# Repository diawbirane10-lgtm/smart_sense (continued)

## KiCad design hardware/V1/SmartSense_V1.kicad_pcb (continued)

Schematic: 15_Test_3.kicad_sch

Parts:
P1, P2, P3: PWR_FLAG; MPN PWR_FLAG

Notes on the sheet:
15 Test 3
Signaux homonymes relies par etiquettes globales ; alimentation 24 V SELV ; prototype a qualifier.
V1 RevA / Validation ERC, DRC et essais du prototype documentes dans le dossier technique.

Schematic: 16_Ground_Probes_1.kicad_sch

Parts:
TP13, TP14, TP15, TP16, TP17, TP18, TP19, TP20: GND; TestPoint_THTPad_D1.0mm_Drill0.5mm; MPN GND probe PCB feature

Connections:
GND: TP13.1, TP14.1, TP15.1, TP16.1, TP17.1, TP18.1, TP19.1, TP20.1; also elsewhere on the board

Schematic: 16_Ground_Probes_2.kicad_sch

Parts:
TP21, TP22, TP23, TP24, TP25, TP26, TP27, TP28: GND; TestPoint_THTPad_D1.0mm_Drill0.5mm; MPN GND probe PCB feature

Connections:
GND: TP21.1, TP22.1, TP23.1, TP24.1, TP25.1, TP26.1, TP27.1, TP28.1; also elsewhere on the board

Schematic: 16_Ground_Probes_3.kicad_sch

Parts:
TP29: GND; TestPoint_THTPad_D1.0mm_Drill0.5mm; MPN GND probe PCB feature

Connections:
GND: TP29.1; also elsewhere on the board

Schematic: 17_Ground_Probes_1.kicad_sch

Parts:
TP30, TP31: GND; TestPoint_THTPad_D1.0mm_Drill0.5mm; MPN GND probe PCB feature

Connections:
GND: TP30.1, TP31.1; also elsewhere on the board

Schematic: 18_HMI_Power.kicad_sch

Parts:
C42: 100u 10V low ESR; CP_Elec_6.3x7.7; MPN EEEFK1A101P
C43: 2.2u 16V X7R; C_0805_2012Metric; MPN C0805C225K4RACTU
C44: 4.7u 10V X7R; C_0805_2012Metric; MPN C0805C475K8RACTU
C47: 100n 100V X7R; C_0805_2012Metric; MPN C0805C104K1RACTU
FB1: 220R@100MHz 2A; R_0805_2012Metric; MPN BLM21PG221SN1D
U13: TLV75533PDBVR; SOT-23-5; MPN TLV75533PDBVR

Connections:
+3V3_HMI: C44.1, U13.5 (OUT); also elsewhere on the board
+5V: FB1.1; also elsewhere on the board
+5V_HMI: C42.1, C43.1, C47.1, FB1.2, U13.1 (IN), U13.3 (EN); also elsewhere on the board
GND: C42.2, C43.2, C44.2, C47.2, U13.2 (GND); also elsewhere on the board

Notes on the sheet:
18 HMI Power
Ecran interne Nextion 2.4 / UART USART1 PA9-PA10 / montage et cables fournis assembles
5V commun: TSR1-4850WI 1A. Branche ecran filtree; C42 polarise (+ au 5V). Essai de charge requis.

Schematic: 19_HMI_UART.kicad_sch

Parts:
C45, C46: 100n 100V X7R; C_0805_2012Metric; MPN C0805C104K1RACTU
R36, R37: 100R 1%; R_0805_2012Metric; MPN RC0805FR-07100RL
R38: 100k 1%; R_0805_2012Metric; MPN RC0805FR-07100KL
U14: TXU0202DCUR; VSSOP-8_2.3x2mm_P0.5mm; MPN TXU0202DCUR

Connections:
+3V3_D: C45.1, U14.3 (VCCA); also elsewhere on the board
+3V3_HMI: C46.1, U14.7 (VCCB); also elsewhere on the board
GND: C45.2, C46.2, R38.2, U14.2 (GND); also elsewhere on the board
HMI_ENABLE: R38.1, U14.6 (OE); also elsewhere on the board
HMI_RX: R36.2; also elsewhere on the board
HMI_RX_SER: R36.1, U14.8 (B1Y)
HMI_TX: R37.1; also elsewhere on the board
HMI_TX_SER: R37.2, U14.1 (B2)
HMI_UART_RX: U14.4 (A2Y); also elsewhere on the board
HMI_UART_TX: U14.5 (A1); also elsewhere on the board

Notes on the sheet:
19 HMI UART
Ecran interne Nextion 2.4 / UART USART1 PA9-PA10 / montage et cables fournis assembles
TXU0202: VCCA=3V3_D, VCCB=3V3_HMI; isolation a alimentation absente. PB7 OE bas au reset.

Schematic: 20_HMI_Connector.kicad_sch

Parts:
J8: HMI:1=5V 2=GND 3=RX 4=TX; JST_XH_B4B-XH-A_1x04_P2.50mm_Vertical; MPN B4B-XH-A(LF)(SN)
TP32: +5V_HMI; TestPoint_Pad_D1.0mm; MPN PCB feature
TP33: +3V3_HMI; TestPoint_Pad_D1.0mm; MPN PCB feature

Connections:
+3V3_HMI: TP33.1; also elsewhere on the board
+5V_HMI: J8.1, TP32.1; also elsewhere on the board
GND: J8.2; also elsewhere on the board
HMI_RX: J8.3; also elsewhere on the board
HMI_TX: J8.4; also elsewhere on the board

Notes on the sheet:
20 HMI Connector
Ecran interne Nextion 2.4 / UART USART1 PA9-PA10 / montage et cables fournis assembles
Faisceau interne <=250mm AWG24. J8/3 vers RX ecran; J8/4 depuis TX ecran. Brancher hors tension.

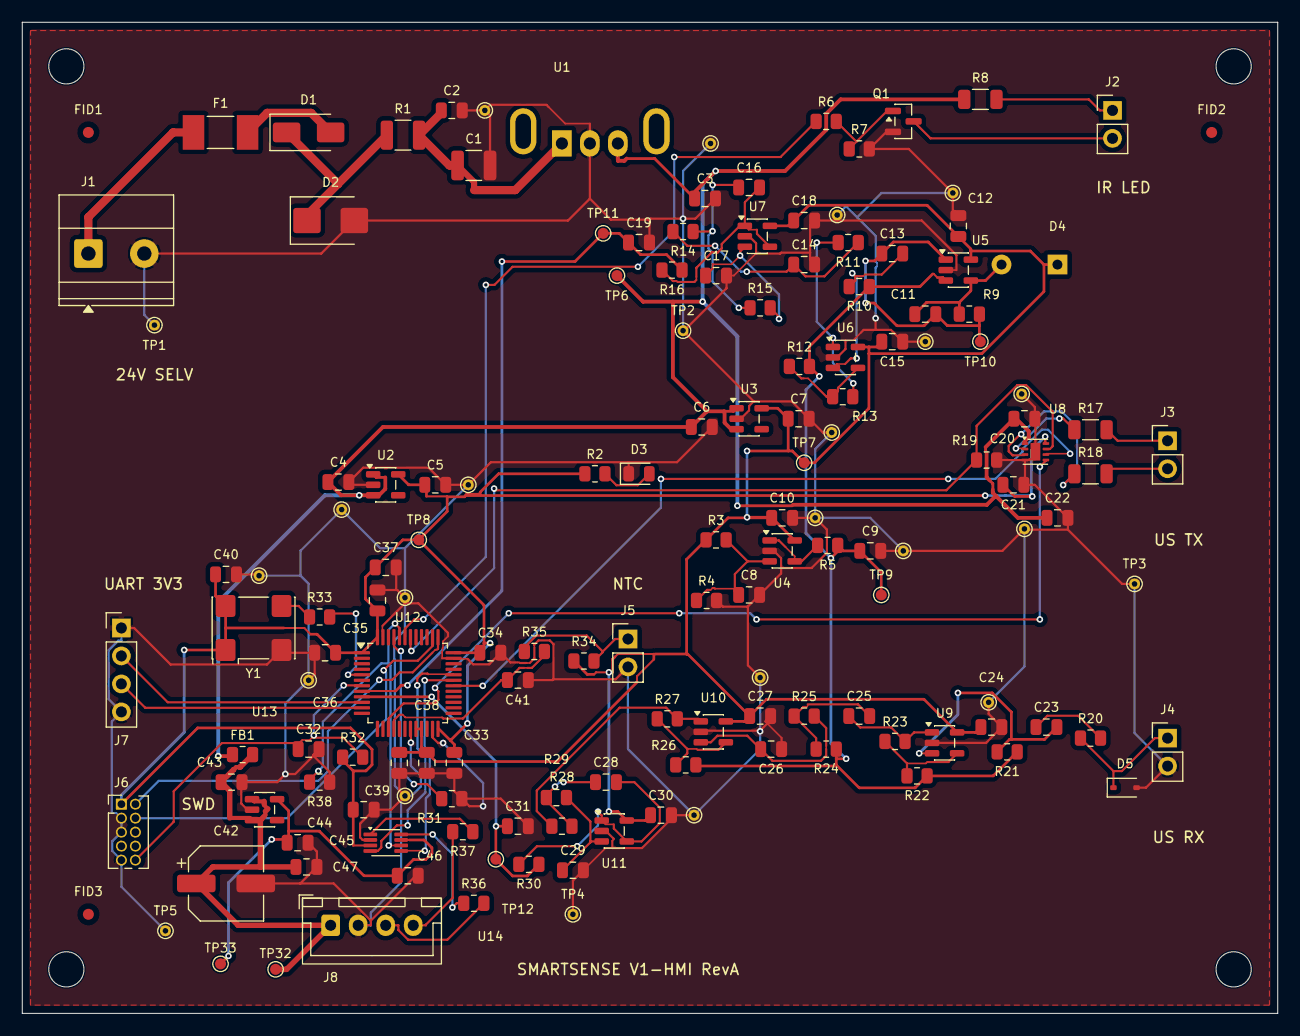
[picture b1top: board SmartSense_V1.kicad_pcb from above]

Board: 4 copper layers, 114.0 x 90.0 mm, 156 parts (0 on the bottom side), 65 nets.

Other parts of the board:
FID1, FID2, FID3: Fiducial_1mm_Mask2mm
